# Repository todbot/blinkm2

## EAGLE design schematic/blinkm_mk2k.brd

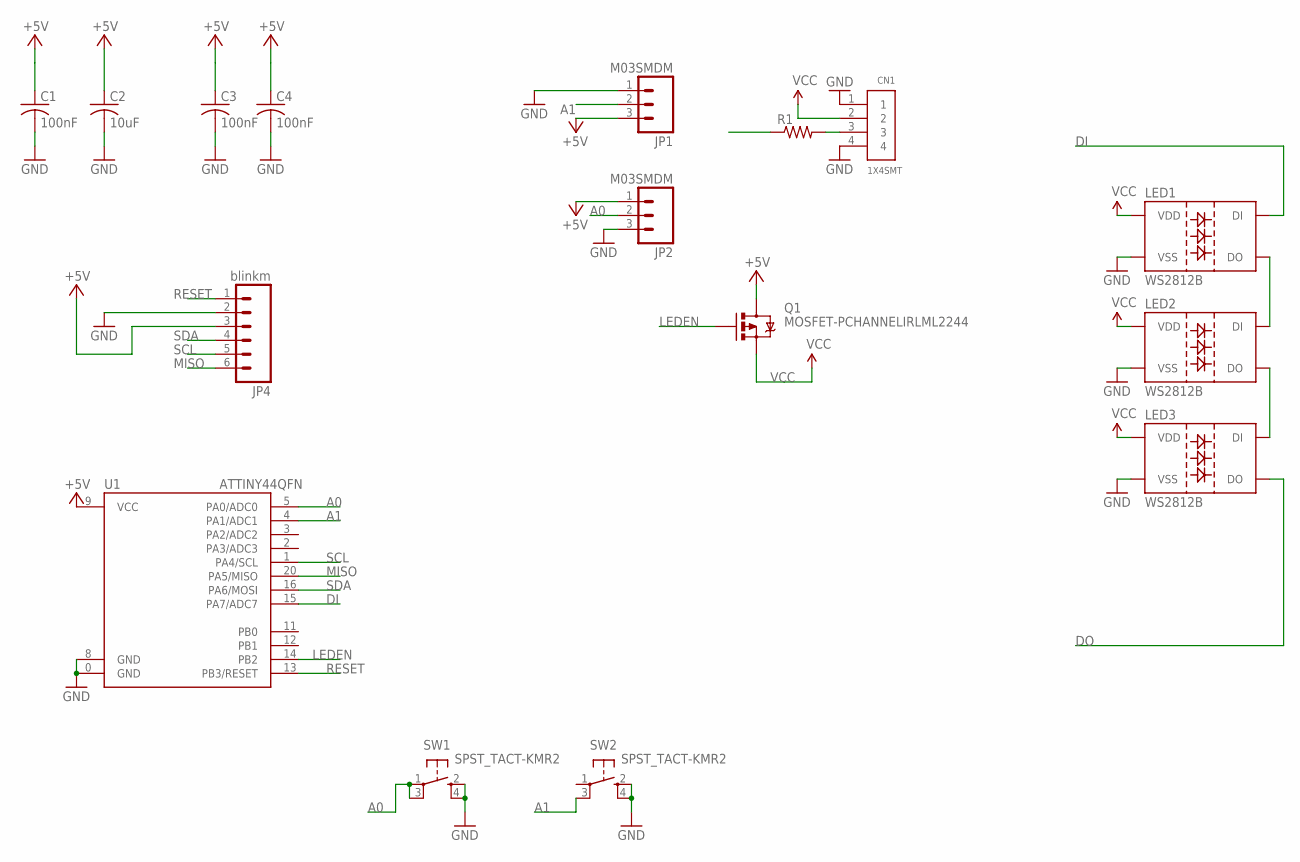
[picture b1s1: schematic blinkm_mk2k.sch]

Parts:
C1, C3, C4: 100nF; C0603
C2: 10uF; C0603
CN1: 1X4SMT; 1X4-SMT
JP1, JP2: M03SMDM; 1X03-SMD-MINIMAL
JP4: blinkm; 1X06_LOCK
LED1, LED2, LED3: WS2812B
Q1: MOSFET-PCHANNELIRLML2244; SOT23-3
R1: RESISTOR0603; 0603-RES
SW1, SW2: SPST_TACT-KMR2; KMR2
U1: ATTINY44QFN; QFN20

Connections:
+5V: C1.1, C2.1, C3.1, C4.1, JP1.3, JP2.1, JP4.3, Q1.3 (D), U1.9 (VCC)
A0: JP2.2, SW1.1, SW1.3 (P1), U1.5 (PA0/ADC0)
A1: JP1.2, SW2.3 (P1), U1.4 (PA1/ADC1)
DI: LED1.4 (DI), R1.1, U1.15 (PA7/ADC7)
DO: LED3.2 (DO)
DOI1: LED1.2 (DO), LED2.4 (DI)
DOI2: LED2.2 (DO), LED3.4 (DI)
GND: C1.2, C2.2, C3.2, C4.2, CN1.1, CN1.4, JP1.1, JP2.3, JP4.2, LED1.3 (VSS), LED2.3 (VSS), LED3.3 (VSS), SW1.2 (S), SW1.4 (S1), SW2.2 (S), SW2.4 (S1), U1.0 (GND), U1.8 (GND)
LEDEN: Q1.1 (G), U1.14 (PB2)
MISO: JP4.6, U1.20 (PA5/MISO)
unnamed: CN1.3, R1.2
RESET: JP4.1, U1.13 (PB3/RESET)
SCL: JP4.5, U1.1 (PA4/SCL)
SDA: JP4.4, U1.16 (PA6/MOSI)
VCC: CN1.2, LED1.1 (VDD), LED2.1 (VDD), LED3.1 (VDD), Q1.2 (S)

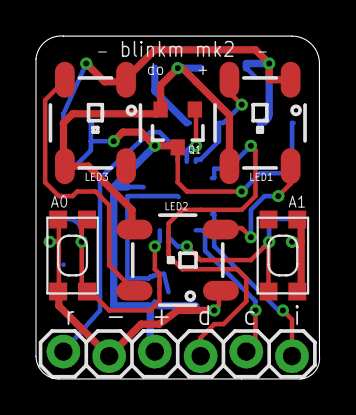
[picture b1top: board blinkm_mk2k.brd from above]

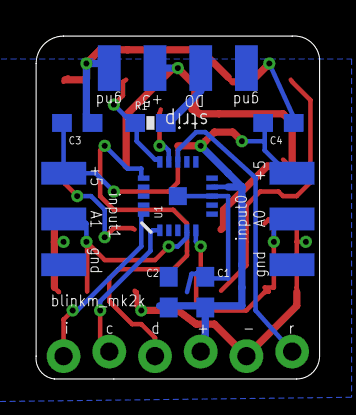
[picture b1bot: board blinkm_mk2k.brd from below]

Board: 2 copper layers, 15.8 x 19.1 mm, 16 parts (9 on the bottom side), 14 nets.

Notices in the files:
parts and their libraries:
SparkFun-Connectors: Licensing: CC v3.0 Share-Alike You are welcome to use this library for commercial purposes.
